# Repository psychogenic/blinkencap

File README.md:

# blinkencap

Blinkencap SAO for hackaday supercon badges

This is a simple badge add-on that uses the massive overkill of an ASIC to blink LEDs.

It was inspired by Matt's famous hat:

so it looks like

and gives you a few interesting ways to blink a LED.  All the circuitry is hidden in the back

It is my entry to the [supercon 8 add-on contest](https://hackaday.io/contest/197237-supercon-8-add-on-contest).

It has a project page on [hackaday.io](https://hackaday.io/project/198371-blinkencap), and the circuit can be opened in KiCad or [found in the docs here](https://raw.githubusercontent.com/psychogenic/blinkencap/main/doc/blinkencap-schematic.pdf), but the preview is

.

This project is

Copyright (C) 2024 Pat Deegan, [psychogenic.com](https://psychogenic.com)

and released under the [CERN-OHL-S](https://cern-ohl.web.cern.ch/home) open hardware license.

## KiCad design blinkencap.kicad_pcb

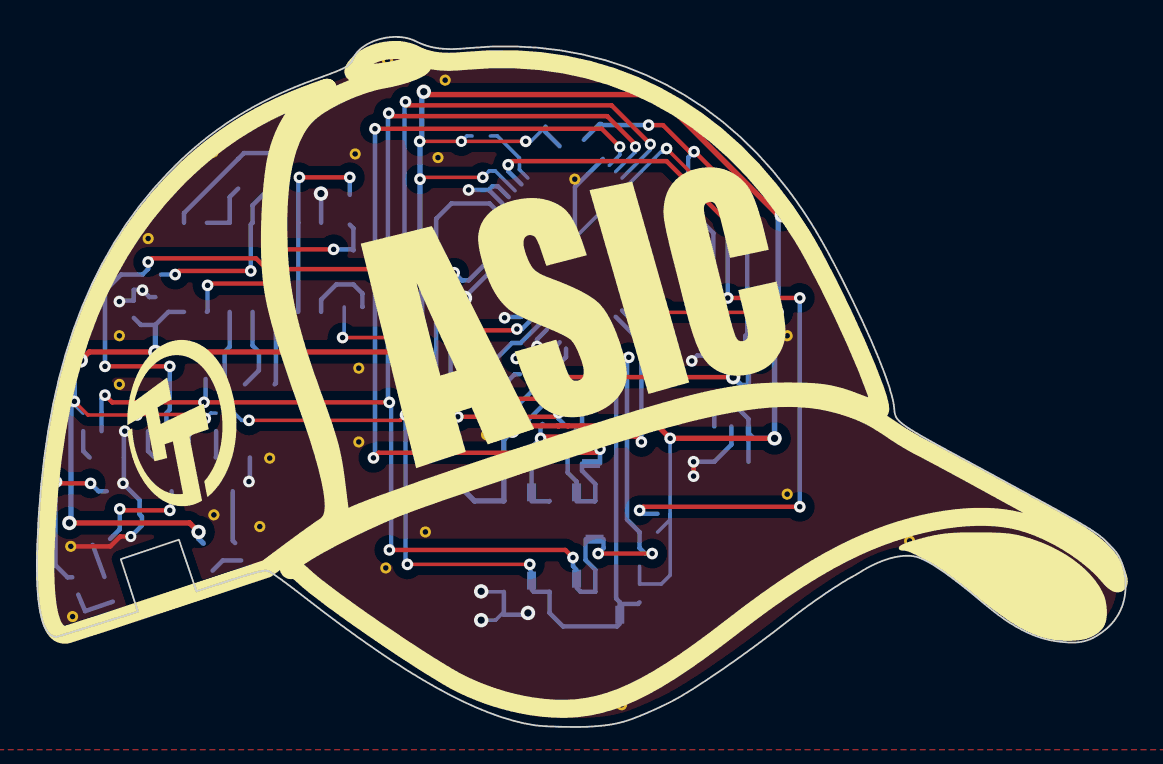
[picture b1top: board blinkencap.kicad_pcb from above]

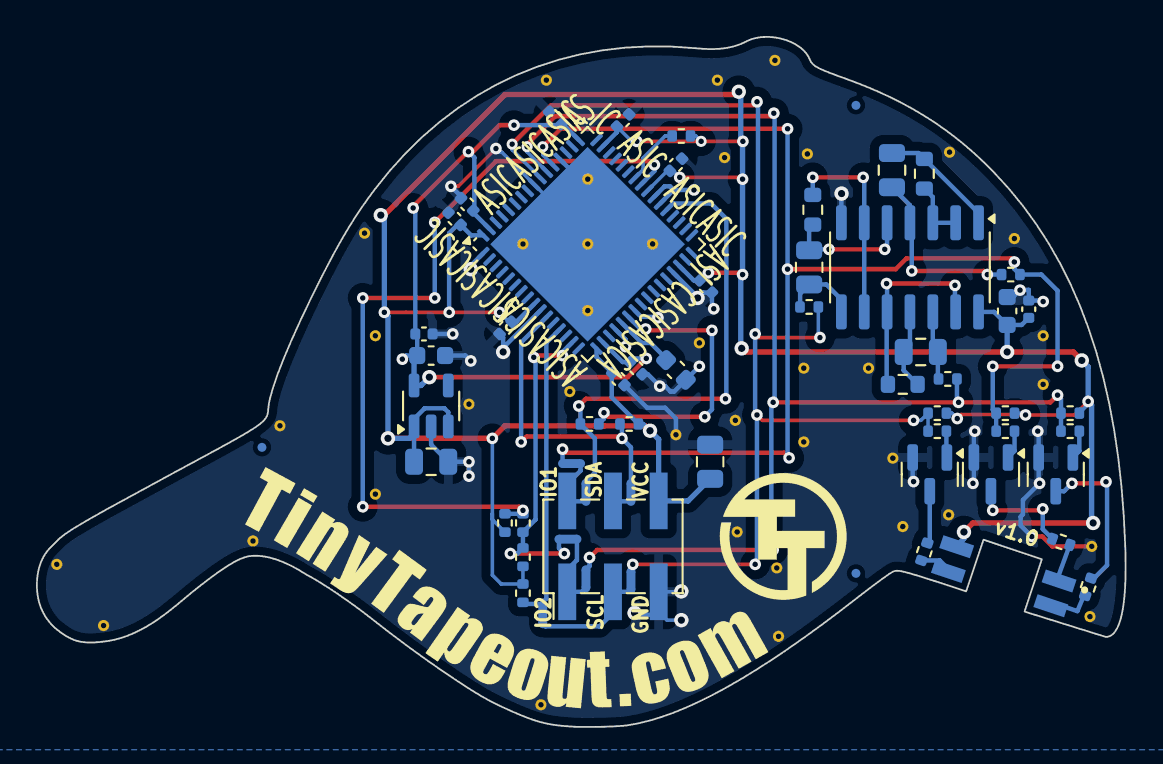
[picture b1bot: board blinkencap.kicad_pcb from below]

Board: 2 copper layers, 60.5 x 38.3 mm, 100 parts (60 on the bottom side), 36 nets.

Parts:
ASICCAP_SILK: asic_capsilk_2
C1, C4: 10uF; C_0805_2012Metric
C2, C14, C15: 1uF; C_0603_1608Metric
C3, C5, C6, C7, C8, C9, C10, C11, C12, C13, C16: 100nF; C_0402_1005Metric
C17, C18, C19: C_470n_0603_50V; C_0805_2012Metric
CAPOUTLINE*: CAPOUTLINE; asic_capoutline_cutout
D1: T36K3BGR-05D000121U1930; LED_T36K3BGR-05D000121U1930
FID1, FID2, FID3: Fiducial; Fiducial_0.5mm_Mask1mm
J1: Conn_02x03_Odd_Even; PinHeader_2x03_P2.54mm_Vertical_SMD
NT1, NT2, NT3, NT4, NT5, NT6, NT7: NetTie_2; NetTie-2_SMD_Pad0.5mm
Q1, Q2, Q3: DMN2005K; SOT-23
R1, R2, R6, R17: R_0R_0402; R_0402_1005Metric
R3, R4, R5, R8, R11, R14: R_10k_0402; R_0402_1005Metric
R7, R10, R13: R_412_0402; R_0402_1005Metric
R9, R12, R15: R_22R_0402; R_0402_1005Metric
R16, R22, R24: R_1M_0603; R_0603_1608Metric
R20, R21, R23: R_1k_0402; R_0402_1005Metric
STITCH1, STITCH1#2, STITCH1#3, STITCH1#4, STITCH1#5, STITCH1#6, STITCH2, STITCH3, STITCH4, STITCH5, STITCH6, STITCH7, STITCH8, STITCH9, STITCH10, STITCH10#2, STITCH11, STITCH12, STITCH12#2, STITCH12#3, STITCH13, STITCH13#2, STITCH14, STITCH15, STITCH16, STITCH17, STITCH18, STITCH19, STITCH20, STITCH21, STITCH21#2, STITCH21#3, STITCH21#4, STITCH21#5, STITCH22, STITCH23, STITCH24, STITCH25: StitchingVia-0.3mm
TTCurvyText: asichat_tttext
U1: AP2112K-1.8; SOT-23-5
U2: Caravel_QFN_TT4; QFN-64-1EP_9x9mm_P0.5mm_EP7.65x7.65mm
U3: SN74HC14DR; SOIC-14_3.9x8.7mm_P1.27mm

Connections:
+1V8: C2.1, C3.1, C5.2, C6.2, C7.2, U1.5 (VOUT), U2.18 (vccd), U2.49 (vccd1), U2.63 (vccd2)
+3V3: C1.1, C4.1, C8.2, C9.2, C10.2, C11.2, C12.2, C13.2, C15.1, C16.1, D1.2, J1.6, R1.1, R3.1, R4.1, R5.1, R8.1, R11.1, R14.1, R17.2, U1.1 (VIN), U1.3 (EN), U2.9 (vdda2), U2.17 (vddio), U2.30 (vdda), U2.40 (vdda1), U2.47 (vdda1), U2.64 (vddio), U3.14 (VCC)
/GPIO1: J1.2, NT1.1, NT5.1
/GPIO2: J1.1, NT2.1, NT6.1
/SCL: J1.3, NT3.1, NT7.1
/SDA: J1.4, NT4.1
/caravel_reset: C14.1, U2.21 (resetb)
/ctrl_ena: NT4.2, R3.2, U2.11 (ctrl_ena/mio[32])
/ctrl_inc: NT3.2, R4.2, U2.13 (ctrl_sel_inc/mio[34])
/drain_blue: Q3.3 (D), R10.2
/drain_green: Q2.3 (D), R13.2
/drain_red: Q1.3 (D), R7.2
/in0: R17.1, U2.42 (ui_in[0]/mio[8])
/led_blue: NT7.2, R14.2, R15.1, R21.2, U2.55 (uo_out[2]/mio[18])
/led_green: NT6.2, R11.2, R12.1, R23.2, U2.54 (uo_out[1]/mio[17])
/led_red: NT5.2, R8.2, R9.1, R20.2, U2.53 (uo_out[0]/mio[16])
/p_clk: NT1.2, R6.1, U2.37 (clk/mio[6])
/~ctrl_rst: NT2.2, R2.2, R5.2, U2.15 (~ctrl_sel_rst/mio[36])
/~p_rst: R1.2, R2.1, U2.41 (~rst/mio[7])
GND: C1.2, C2.2, C3.2, C4.2, C5.1, C6.1, C7.1, C8.1, C9.1, C10.1, C11.1, C12.1, C13.1, C14.2, C15.2, C16.2, J1.5, Q1.2 (S), Q2.2 (S), Q3.2 (S), STITCH1.1, STITCH1#2.1, STITCH1#3.1, STITCH1#4.1, STITCH1#5.1, STITCH1#6.1, STITCH2.1, STITCH3.1, STITCH4.1, STITCH5.1, STITCH6.1, STITCH7.1, STITCH8.1, STITCH9.1, STITCH10.1, STITCH10#2.1, STITCH11.1, STITCH12.1, STITCH12#2.1, STITCH12#3.1, STITCH13.1, STITCH13#2.1, STITCH14.1, STITCH15.1, STITCH16.1, STITCH17.1, STITCH18.1, STITCH19.1, STITCH20.1, STITCH21.1, STITCH21#2.1, STITCH21#3.1, STITCH21#4.1, STITCH21#5.1, STITCH22.1, STITCH23.1, STITCH24.1, STITCH25.1, U1.2 (GND), U2.1 (vssa2), U2.10 (vssd2), U2.20 (vssa), U2.23 (vssd), U2.29 (vssio), U2.38 (vssa1), U2.39 (vssd1), U2.52 (vssa1), U2.56 (vssio), U2.65 (ThermalPad), U3.7 (GND)
unnamed: C17.1, R20.1, U3.4
unnamed: C17.2, R16.2, U3.1
unnamed: C18.1, R21.1, U3.8
unnamed: C18.2, R22.2, U3.5
unnamed: C19.1, R23.1, U3.12
unnamed: C19.2, R24.2, U3.11
unnamed: D1.1, R7.1
unnamed: D1.3, R10.1
unnamed: D1.4, R13.1
unnamed: Q1.1 (G), R9.2
unnamed: Q2.1 (G), R12.2
unnamed: Q3.1 (G), R15.2
unnamed: R16.1, U3.2, U3.3
unnamed: R22.1, U3.6, U3.9
unnamed: R24.1, U3.10, U3.13
unnamed: R6.2, U2.22 (clock)

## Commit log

2024-10-09 preliminary commit
2024-10-09 documentation and license
2024-10-18 uPython driver for ASIC populated caps
